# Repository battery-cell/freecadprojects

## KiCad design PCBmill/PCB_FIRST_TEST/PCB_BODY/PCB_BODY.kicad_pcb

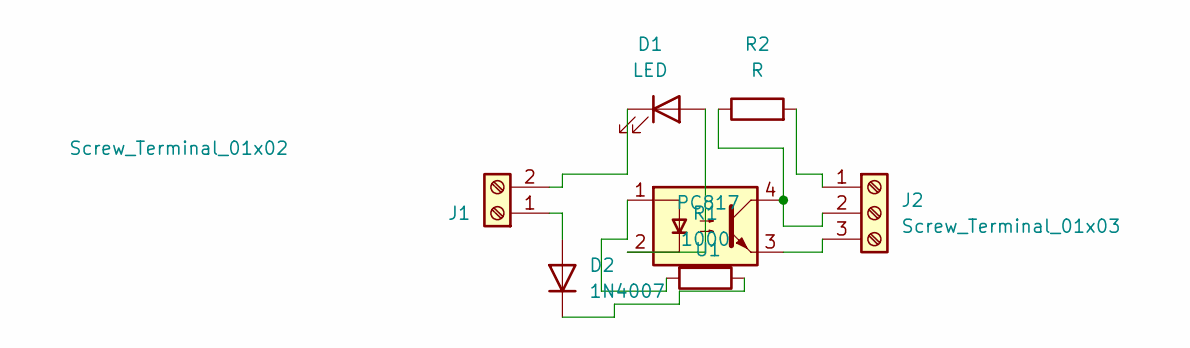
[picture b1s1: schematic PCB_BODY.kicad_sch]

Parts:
D1: LED; LED_D1.8mm_W3.3mm_H2.4mm
D2: 1N4007; D_DO-41_SOD81_P10.16mm_Horizontal
J1: Screw_Terminal_01x02; TerminalBlock_MaiXu_MX126-5.0-02P_1x02_P5.00mm
J2: Screw_Terminal_01x03; TerminalBlock_MaiXu_MX126-5.0-03P_1x03_P5.00mm
R1: 1000; R_Axial_DIN0207_L6.3mm_D2.5mm_P5.08mm_Vertical
R2: R; R_Axial_DIN0207_L6.3mm_D2.5mm_P5.08mm_Vertical
U1: PC817; DIP-4_W7.62mm

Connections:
unnamed: D1.2 (A), U1.2
unnamed: D1.1 (K), J1.2
unnamed: D2.2 (A), J1.1
unnamed: D2.1 (K), R1.1
unnamed: J2.1, R2.2
unnamed: J2.2, R2.1, U1.4
unnamed: J2.3, U1.3
unnamed: R1.2, U1.1

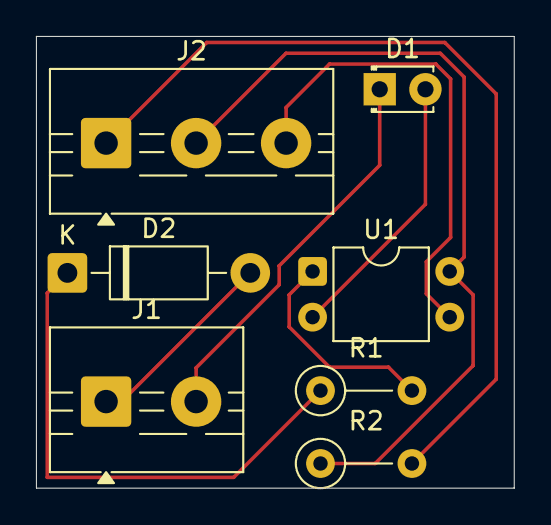
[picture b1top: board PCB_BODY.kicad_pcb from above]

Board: 2 copper layers, 26.5 x 25.1 mm, 7 parts (0 on the bottom side), 8 nets.

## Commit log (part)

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2026-04-06 first commit i guess
2026-04-08 im bouta cry
2026-04-08 tried to make the shell
2026-04-09 1232
2026-04-13 commited to the grind
2026-04-19 windernator
2026-05-29 added
2026-05-31 IM TWEAKING
2026-06-02 LESGOO
2026-06-02 made that toofy gear
2026-06-07 i kinda helped my brother out with the freecad model i guess
2026-06-08 here we go
2026-06-11 new revision
